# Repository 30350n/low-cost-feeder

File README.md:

# Low Co$t Feeder

This is a cost optimized version of the original LumenPnP Feeders by
[Opulo](https://www.opulo.io/).

## Warning: This is still highly experimental, PCBs haven't been ordered/tested at all yet.

### Changes:

- **3.3V -> 5V mcu/logic supply**  
  The original RS485 transceiver costs 6-7€ in Qty 10, alternative parts that can be powered
  by 3.3V start at 3-4€. Similar 5V powered parts are already available for ~1€.
- **STM32F031 -> ATmega328PB**  
  The ATmega328P is just the first MCU I could think of that's 5V compatible and has just enough
  IO, is available in similar packages (TQFP and QFN), is similarly priced and should be able to
  run the photon firmware just fine. The ATmega328PB is not a drop in replacement, but has extra
  features (like UUID support) and is even cheaper.
- **470uF -> 100uF buck converter output capacitor**  
  There are very few 470uF 10V capable caps available in the specified package. The 470uF cap
  is also very overspecd, 100uF should be totally sufficient for the application. (The original
  value probably got copied straight from the datasheet example schematic.)
- **Countersinks -> [24882 solderable standoffs](https://www.digikey.com/en/products/detail/keystone-electronics/24882/9921841)**  
  Getting the countersinks done by the PCB manufacturer is probably way to expensive,
  especially for low qty orders. The standoffs would add a cost of ~2.5€ per board.
  Alternatively it might be possible to use a 3D print with standard M3 nuts/heat set inserts,
  glued to the PCB in their place.  
  Adding the countersinks to the holes yourself is still possible too.
- **Option to bypass the onboard SMPS** (thanks @FL140 for the idea!)  
  Added a 0R resistor to bypass the onboard SMPS for **users of +12V machines**. This should
  save 1-2€ in components and might also have some other benefits, like better EMC.  
  **If this option is being used, the DRV8837 motor drivers should be replaced with +12V
  tolerant ones, for example DRV8220.**

## LumenPnP Feeders
The LumenPnP Feeders are open source pick and place feeders to aid in [Mid-Scale Manufacturing](https://stephenhawes.com/level-2-manufacturing/).

LumenPnP Feeders are available for sale on the [Opulo Website](https://www.opulo.io/). If you build or buy one, please help the project by documenting bugs with a GitHub issue.

The LumenPnP Feeders run [Photon](https://github.com/photonfirmware/photon), an open source firmware project for pick and place feeders. The popular pick and place control software [OpenPnP](https://openpnp.org/) has Photon support built in, so it's easy to get going with the LumenPnP feeders using your existing OpenPnP setup. These feeders are designed to work with the [LumenPnP](https://opulo.io/products/lumenpnp).

The development process is being cataloged in a series of videos. A playlist of these can be found [here](https://www.youtube.com/playlist?list=PLIeJXmcg1baLBz3x0nCDqkYpKs2IWGHk4).

### Documentation
Feeder user documentation can be found on the [Opulo Docs Page](https://docs.opulo.io/). Open Hardware Assembly instructions can be found at [ohai.opulo.io](https://ohai.opulo.io/).

### Community
Discussion about the project happens on the [STR Discord server](https://discordapp.com/invite/TCwy6De)!

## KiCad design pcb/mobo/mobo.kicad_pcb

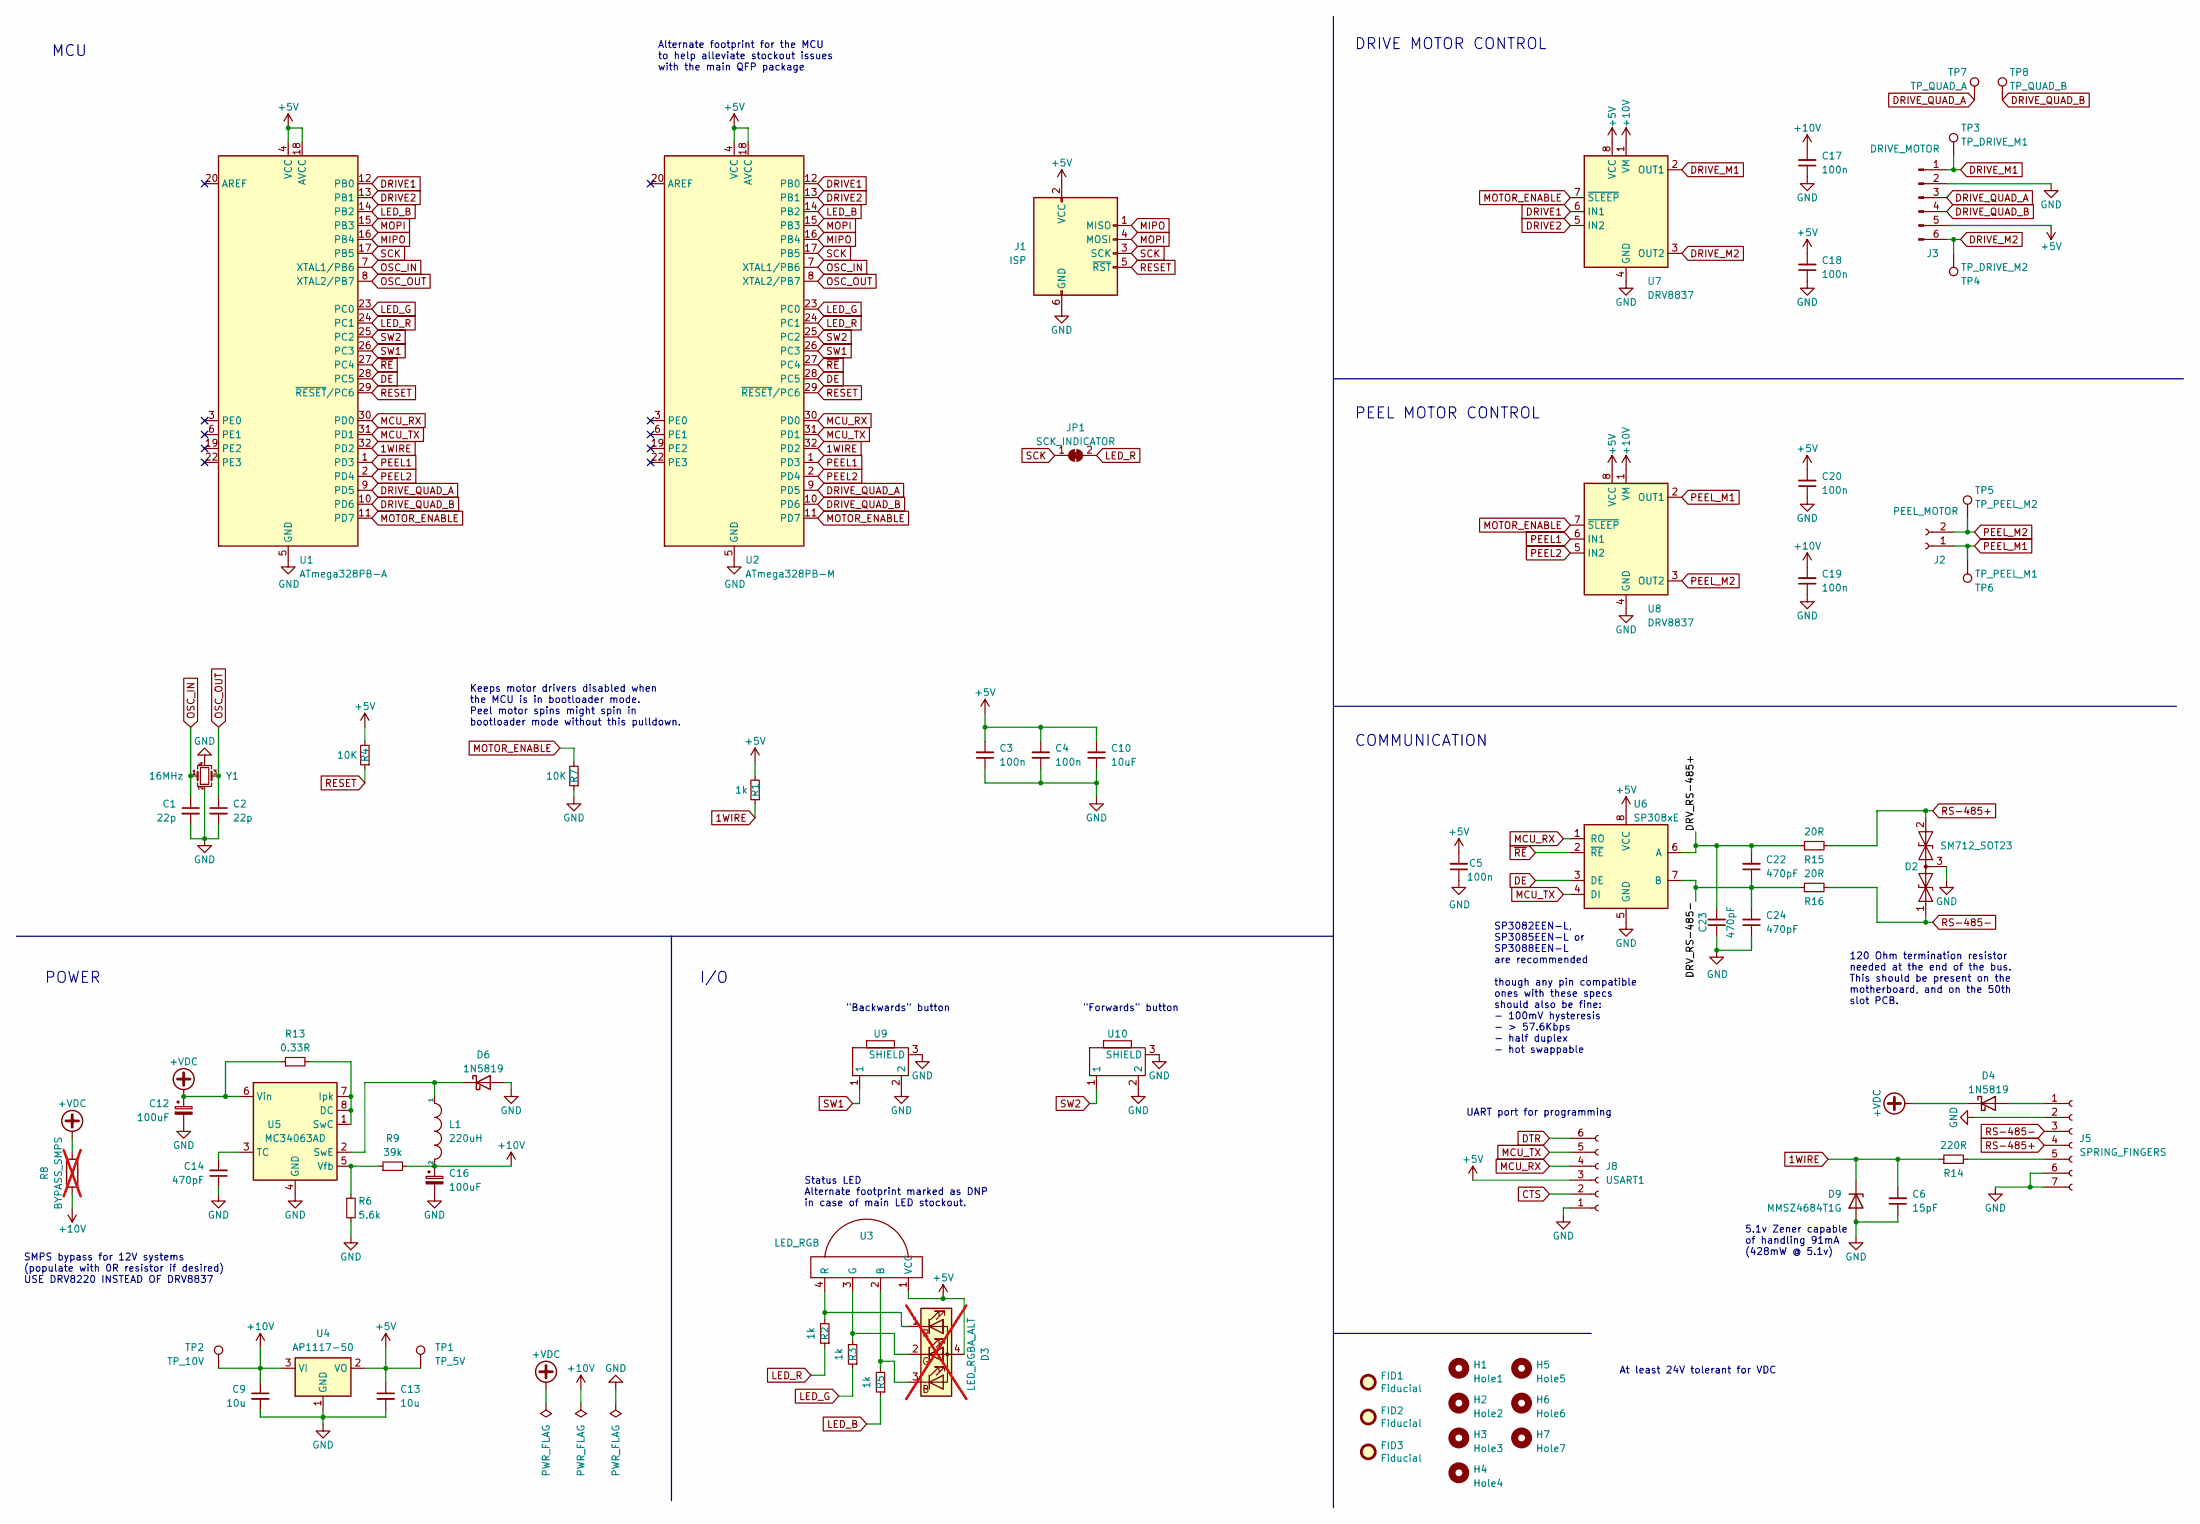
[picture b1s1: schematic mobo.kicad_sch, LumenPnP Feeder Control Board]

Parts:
C1, C2: 22p; C_0805_2012Metric; JLCPCB C1794
C3, C4, C5, C17, C18, C19, C20: 100n; C_0805_2012Metric; JLCPCB C49678
C6: 15pF; C_0805_2012Metric; JLCPCB C49678
C9, C13: 10u; C_0805_2012Metric; JLCPCB C15850
C10: 10uF; C_0805_2012Metric; JLCPCB C49678
C12, C16: 100uF; C_Elec_6.3x7.7
C14, C22, C23, C24: 470pF; C_0805_2012Metric; JLCPCB C49678
D2: SM712_SOT23; SOT-23; LCSC C521963
D3: LED_RGBA_ALT; LED_LiteOn_LTST-C19HE1WT; not fitted
D4, D6: 1N5819; D_SOD-123
D9: MMSZ4684T1G; D_SOD-123; JLCPCB MMSZ4684T1G
FID1, FID2, FID3: Fiducial; Fiducial_1mm_Mask2mm
H1: Hole1; MountingHole_4.2mm_24822
H2: Hole2; MountingHole_4.2mm_24822
H3: Hole3; MountingHole_4.2mm_24822
H4: Hole4; MountingHole_4.2mm_24822
H5: Hole5; MountingHole_4.2mm_24822
H6: Hole6; MountingHole_4.2mm_24822
H7: Hole7; MountingHole_4.2mm_24822
J1: ISP; ISP_FRICTION_FIT
J2: PEEL_MOTOR; Molex_PicoBlade_53261-0271_1x02-1MP_P1.25mm_Horizontal; LCSC C2845379
J3: DRIVE_MOTOR; Molex_PicoBlade_53261-0671_1x06-1MP_P1.25mm_Horizontal; LCSC C2845383
J5: SPRING_FINGERS; AVX-9155-005-541
J8: USART1; UART_FRICTION_FIT
JP1: SCK_INDICATOR; SolderJumper-2_P1.3mm_Bridged_RoundedPad1.0x1.5mm
L1: 220uH; L_6.3x6.3_H3; LCSC C467145
R1: 1k; R_0805_2012Metric; JLCPCB C17513
R2, R3, R5: 1k; R_0805_2012Metric; JLCPCB C17710
R4, R7: 10K; R_0805_2012Metric; JLCPCB C17513
R6: 5.6k; R_0805_2012Metric
R8: BYPASS_SMPS; R_0805_2012Metric; not fitted
R9: 39k; R_0805_2012Metric
R13: 0.33R; R_0805_2012Metric
R14: 220R; R_0805_2012Metric
R15, R16: 20R; R_0805_2012Metric
TP1: TP_5V; TestPoint_Pad_D2.0mm
TP2: TP_10V; TestPoint_Pad_D2.0mm
TP3: TP_DRIVE_M1; TestPoint_Pad_D2.0mm
TP4: TP_DRIVE_M2; TestPoint_Pad_D2.0mm
TP5: TP_PEEL_M2; TestPoint_Pad_D2.0mm
TP6: TP_PEEL_M1; TestPoint_Pad_D2.0mm
TP7: TP_QUAD_A; TestPoint_Pad_D2.0mm
TP8: TP_QUAD_B; TestPoint_Pad_D2.0mm
U1: ATmega328PB-A; TQFP-32_7x7mm_P0.8mm
U2: ATmega328PB-M; QFN-32-1EP_5x5mm_P0.5mm_EP3.1x3.1mm_DNP
U3: LED_RGB; MHS110FRGBCT
U4: AP1117-50; SOT-223-3_TabPin2
U5: MC34063AD; SOIC-8_3.9x4.9mm_P1.27mm
U6: SP308xE; SOIC-8_3.9x4.9mm_P1.27mm
U7, U8: DRV8837; WSON-8-1EP_2x2mm_P0.5mm_EP0.9x1.6mm
U9, U10: 1TS003B-1400-3500A-CT
Y1: 16MHz; Crystal_SMD_3225-4Pin_3.2x2.5mm_HandSoldering; JLCPCB C253751

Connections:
1WIRE: C6.2, D9.1 (K), R1.1, R14.1, U1.32 (PD2), U2.32 (PD2)
+5V: C3.2, C4.2, C5.2, C10.2, C13.1, C18.2, C20.2, D3.4 (A), J1.2 (VCC), J3.5, J8.3, R1.2, R4.2, TP1.1, U1.4 (VCC), U1.18 (AVCC), U2.4 (VCC), U2.18 (AVCC), U3.1 (VCC), U4.2 (VO), U6.8 (VCC), U7.8 (VCC), U8.8 (VCC)
+10V: C9.1, C16.1, C17.2, C19.2, L1.2, R8.2, R9.2, TP2.1, U4.3 (VI), U7.1 (VM), U8.1 (VM)
+VDC: C12.1, D4.1 (K), R8.1, R13.1, U5.6 (Vin)
/DRV_RS-485+: C22.2, C23.2, R15.1, U6.6 (A)
/DRV_RS-485-: C22.1, C24.2, R16.1, U6.7 (B)
CTS: J8.2
DE: U1.28 (PC5), U2.28 (PC5), U6.3 (DE)
DRIVE1: U1.12 (PB0), U2.12 (PB0), U7.6 (IN1)
DRIVE2: U1.13 (PB1), U2.13 (PB1), U7.5 (IN2)
DRIVE_M1: J3.1, TP3.1, U7.2 (OUT1)
DRIVE_M2: J3.6, TP4.1, U7.3 (OUT2)
DRIVE_QUAD_A: J3.3, TP7.1, U1.9 (PD5), U2.9 (PD5)
DRIVE_QUAD_B: J3.4, TP8.1, U1.10 (PD6), U2.10 (PD6)
DTR: J8.6
GND: C1.2, C2.2, C3.1, C4.1, C5.1, C6.1, C9.2, C10.1, C12.2, C13.2, C14.1, C16.2, C17.1, C18.1, C19.1, C20.1, C23.1, C24.1, D2.3 (common), D6.2 (A), D9.2 (A), J1.6 (GND), J3.2, J5.2, J5.6, J5.7, J8.1, R6.2, R7.1, U1.5 (GND), U1.21 (GND), U2.5 (GND), U2.21 (GND), U2.33 (GND), U4.1 (GND), U5.4 (GND), U6.5 (GND), U7.4 (GND), U7.9 (GND), U8.4 (GND), U8.9 (GND), U9.2, U9.3 (SHIELD), U10.2, U10.3 (SHIELD), Y1.2, Y1.4
LED_B: R5.1, U1.14 (PB2), U2.14 (PB2)
LED_G: R3.1, U1.23 (PC0), U2.23 (PC0)
LED_R: JP1.2 (B), R2.1, U1.24 (PC1), U2.24 (PC1)
MCU_RX: J8.4, U1.30 (PD0), U2.30 (PD0), U6.1 (RO)
MCU_TX: J8.5, U1.31 (PD1), U2.31 (PD1), U6.4 (DI)
MIPO: J1.1 (MISO), U1.16 (PB4), U2.16 (PB4)
MOPI: J1.4 (MOSI), U1.15 (PB3), U2.15 (PB3)
MOTOR_ENABLE: R7.2, U1.11 (PD7), U2.11 (PD7), U7.7 (~SLEEP), U8.7 (~SLEEP)
unnamed: D3.3 (BK), R5.2, U3.2 (B)
unnamed: D3.2 (GK), R3.2, U3.3 (G)
unnamed: D3.1 (RK), R2.2, U3.4 (R)
unnamed: D4.2 (A), J5.1
unnamed: D6.1 (K), L1.1, U5.2 (SwE)
unnamed: J5.5, R14.2
unnamed: R13.2, U5.1 (SwC), U5.7 (Ipk), U5.8 (DC)
unnamed: C14.2, U5.3 (TC)
unnamed: R6.1, R9.1, U5.5 (Vfb)
OSC_IN: C1.1, U1.7 (XTAL1/PB6), U2.7 (XTAL1/PB6), Y1.1
OSC_OUT: C2.1, U1.8 (XTAL2/PB7), U2.8 (XTAL2/PB7), Y1.3
PEEL1: U1.1 (PD3), U2.1 (PD3), U8.6 (IN1)
PEEL2: U1.2 (PD4), U2.2 (PD4), U8.5 (IN2)
PEEL_M1: J2.1, TP6.1, U8.2 (OUT1)
PEEL_M2: J2.2, TP5.1, U8.3 (OUT2)
RESET: J1.5 (~RST), R4.1, U1.29 (~RESET/PC6), U2.29 (~RESET/PC6)
RS-485+: D2.2 (A2), J5.4, R15.2
RS-485-: D2.1 (A1), J5.3, R16.2
SCK: J1.3 (SCK), JP1.1 (A), U1.17 (PB5), U2.17 (PB5)
SW1: U1.26 (PC3), U2.26 (PC3), U9.1
SW2: U1.25 (PC2), U2.25 (PC2), U10.1
~RE: U1.27 (PC4), U2.27 (PC4), U6.2 (~RE)

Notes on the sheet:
SMPS bypass for 12V systems (populate with 0R resistor if desired) USE DRV8220 INSTEAD OF DRV8837
"Backwards" button
DRIVE MOTOR CONTROL
Status LED Alternate footprint marked as DNP in case of main LED stockout.
PEEL MOTOR CONTROL
120 Ohm termination resistor needed at the end of the bus. This should be present on the motherboard, and on the 50th slot PCB.
I/O
MCU
SP3082EEN-L, SP3085EEN-L or SP3088EEN-L are recommended though any pin compatible ones with these specs should also be fine: - 100mV hysteresis - > 57.6Kbps - half duplex - hot swappable
5.1v Zener capable of handling 91mA (428mW @ 5.1v)
"Forwards" button
At least 24V tolerant for VDC
Keeps motor drivers disabled when the MCU is in bootloader mode. Peel motor spins might spin in bootloader mode without this pulldown.
POWER
Alternate footprint for the MCU to help alleviate stockout issues with the main QFP package
UART port for programming
COMMUNICATION

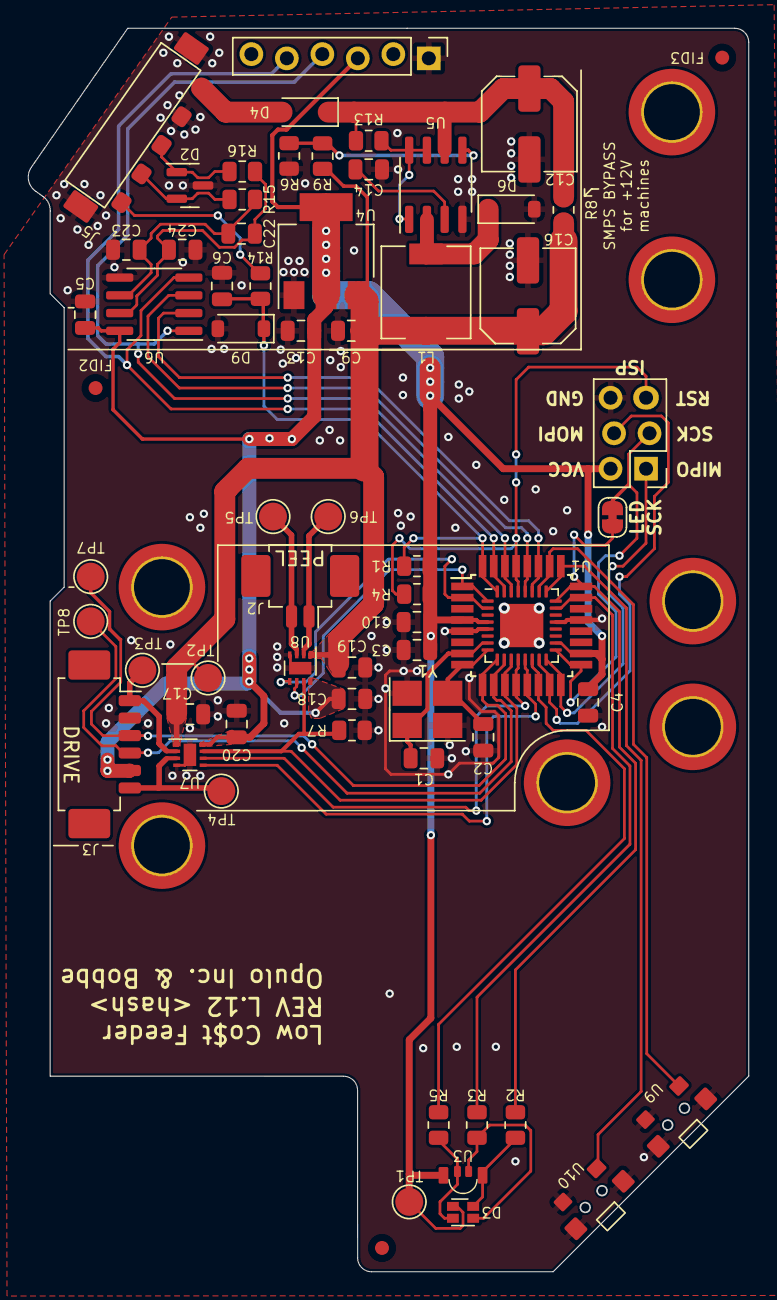
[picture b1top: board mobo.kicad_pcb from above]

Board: 2 copper layers, 51.6 x 89.0 mm, 73 parts (0 on the bottom side), 44 nets.

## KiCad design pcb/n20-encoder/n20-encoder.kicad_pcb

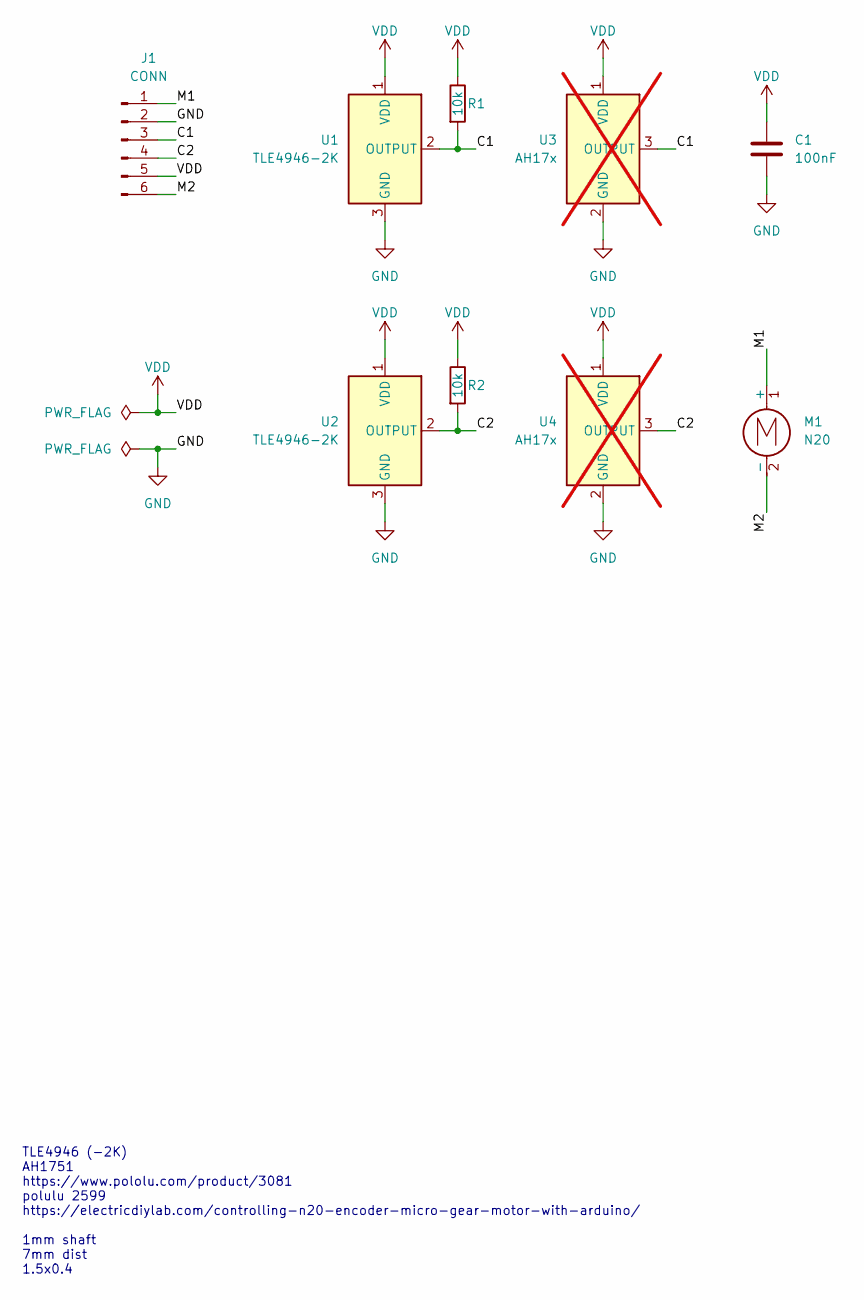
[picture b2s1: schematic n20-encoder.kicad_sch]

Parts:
C1: 100nF; C_0603_1608Metric
J1: CONN; JST_ZH_B6B-ZR-A_1x06_P1.50mm_Vertical
M1: N20; CHF-GW12T-N20VA
R1, R2: 10k; R_0603_1608Metric
U1, U2: TLE4946-2K; SC-59
U3, U4: AH17x; SIP-3_4.1x1.5mm_P1.27mm; not fitted

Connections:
/C1: J1.3, R1.2, U1.2 (OUTPUT), U3.3 (OUTPUT)
/C2: J1.4, R2.2, U2.2 (OUTPUT), U4.3 (OUTPUT)
/M1: J1.1, M1.1 (+)
/M2: J1.6, M1.2 (-)
GND: C1.2, J1.2, U1.3 (GND), U2.3 (GND), U3.2 (GND), U4.2 (GND)
VDD: C1.1, J1.5, R1.1, R2.1, U1.1 (VDD), U2.1 (VDD), U3.1 (VDD), U4.1 (VDD)

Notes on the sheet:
TLE4946 (-2K) AH1751 https://www.pololu.com/product/3081 polulu 2599 https://electricdiylab.com/controlling-n20-encoder-micro-gear-motor-with-arduino/ 1mm shaft 7mm dist 1.5x0.4

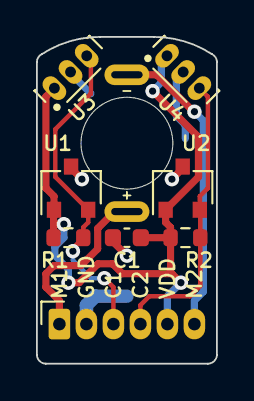
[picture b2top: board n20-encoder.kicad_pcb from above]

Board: 2 copper layers, 10.0 x 18.2 mm, 9 parts (0 on the bottom side), 6 nets.

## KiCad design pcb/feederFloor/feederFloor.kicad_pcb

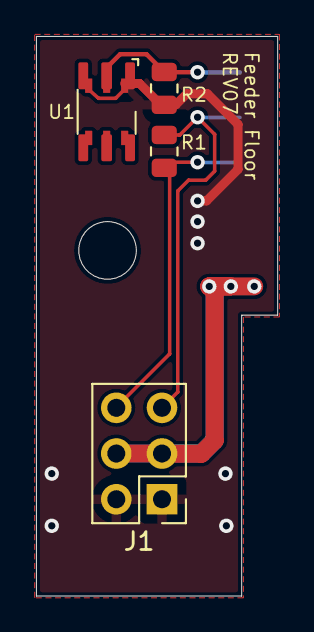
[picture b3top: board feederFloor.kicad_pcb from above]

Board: 2 copper layers, 13.4 x 31.1 mm, 6 parts (1 on the bottom side), 5 nets.

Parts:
H1: MountingHole; MountingHole_3.2mm_M3
J1: IDC; PinHeader_2x03_P2.54mm_Vertical
J2: Conn_01x05_Female; AVX-915-005-541-Contact-Surface
R1: 120R; R_0805_2012Metric
R2: 1M; R_0805_2012Metric
U1: DS28E07; DS28E07_MULTI

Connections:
1WIRE: J2.1, R2.1, U1.2 (IO)
GND: J1.1, J1.2, J2.4, R2.2, U1.1 (GND)
RS-485+: J1.5, J2.2, R1.2
RS-485-: J1.6, J2.3, R1.1
VIN: J1.3, J1.4, J2.5

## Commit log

2023-04-05 Cost optimize main feeder pcb
    - Change mcu/logic supply to 5V instead of 3.3V
    - Use atmega328p as mcu
    - Use SP308xE as RS485 transceiver
    - Use 100uF output capacitor for buck coverter
    - Make it possible to use solderable standoffs instead of chamfers
2023-04-06 Add changelog/motivation to README
2023-04-06 Fix standoff link in README
2023-04-25 Add decoupling cap for RS-485 transceiver, Set edge clearance to 0.2mm
2023-04-25 Add n20 encoder board
2023-04-26 Add diode for reverse polarity protection, Add SMPS bypass jumper
2023-04-26 Add documentation for SMPS bypass to README
2023-04-26 Add newline to README
2023-04-26 Add another newline
2023-04-26 Replace bypass jumper with 0R resistor
2023-04-26 Exclude courtyard violations
2023-05-10 Cleanup tracks and vias
2023-05-10 Replace ATmega328P with ATmega328PB and improve RS-485 routing
2023-06-02 Replace n20-encoder edge cuts hole with drill, improve routing
2023-06-02 Remove unused libraries, Make feeder lib path relative
2023-06-03 Remove vias from pads, Remove paste layer from alt QFN footprint (#14)
2023-06-03 Improve driver power routing by adding filled zones
2023-06-03 Add X and Y caps to RS485 lines (#19), Update symbols
2023-06-03 Mark LED_RGBA_ALT as DNP, Add MHS110FRGBCT symbol, footprint (#9)
2023-06-03 Add push button symbol, Update footprints, Cleanup tracks
2023-06-03 Rearrange schematic and add annotations
2023-06-03 Remove copper pour from spring finger protector
2023-06-03 Cleanup silkscreen
2023-06-03 Add keepout area for counter sinks to mounting holes
2023-06-03 Update .gitignore to KiCad 7.0, Remove backup, prl files
2023-06-03 Invert light diffusion board logo, fix lib table
2023-06-04 Fix plot settings for light diffusion board (prev. commit fixed #33)
2023-06-04 Set n20 encoder stackup, plot settings
2023-06-04 Update feeder floor, Add silkscreen for hand labeling, Fix design rules
2023-06-04 Fix indexing wheel design rules, Set stackup, plot settings
2023-06-04 Set light diffusion board stackup
2023-06-04 Fix fiducial board design rules, Set stackup, plot settings
2023-06-04 Add power flags to mobo to fix ERC errors
2023-06-04 Set mobo stackup, plot settings
2023-06-18 Add parametric feeder frame
2023-06-18 Fix feeder frame component tape overhang
2023-06-19 Make parametric feeders thicker if possible, Improve pick window size
2023-06-20 Fix drive motor not fitting into parametric feeder frame
2023-06-20 Make feeder frame cover tape guide adjustable, Fix max feeder width
